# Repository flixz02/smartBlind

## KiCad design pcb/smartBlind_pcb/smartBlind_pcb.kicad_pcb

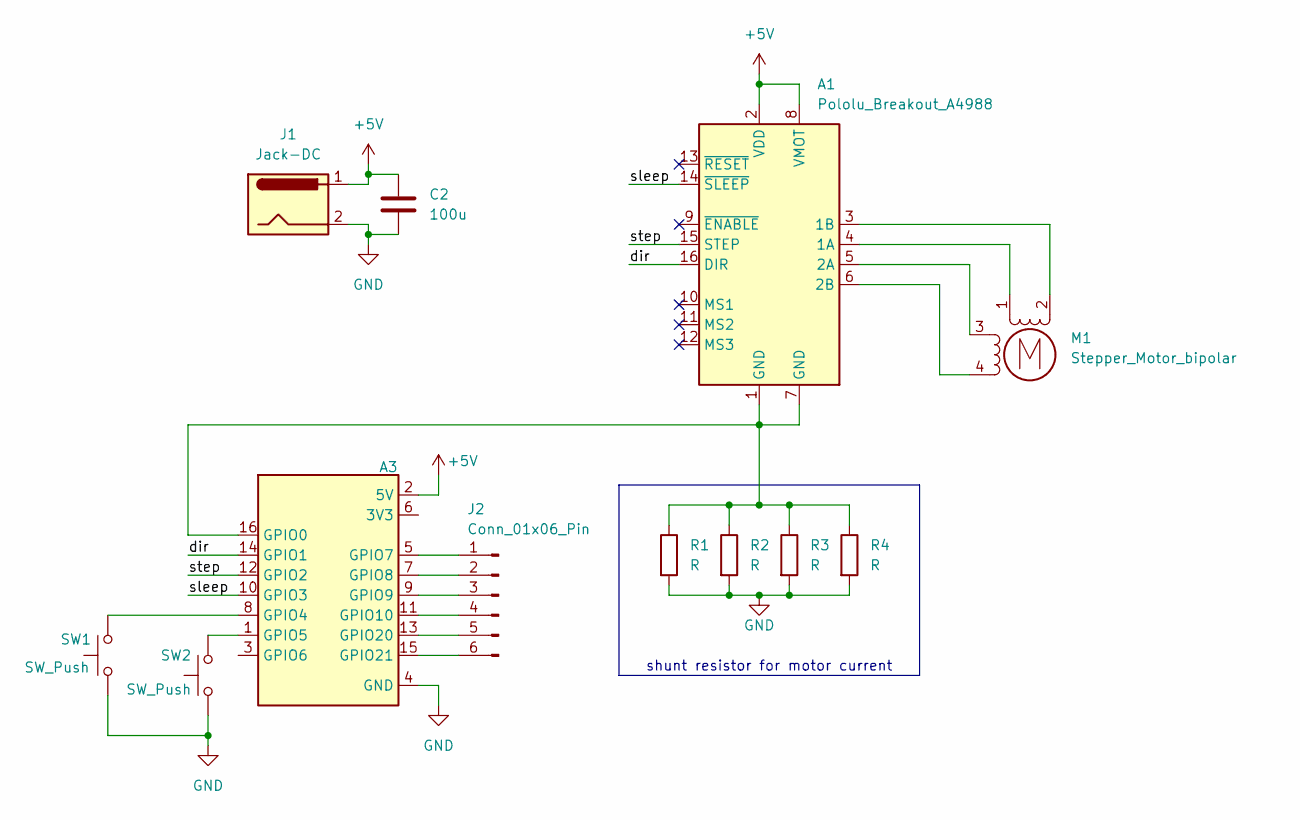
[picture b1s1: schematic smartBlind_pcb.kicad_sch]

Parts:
A1: Pololu_Breakout_A4988; Pololu_Breakout-16_15.2x20.3mm
A3: esp32-c3-supermini
C2: 100u; CP_Radial_D8.0mm_P2.50mm
J1: Jack-DC; PinHeader_1x02_P2.54mm_Vertical
J2: Conn_01x06_Pin; PinHeader_1x06_P2.54mm_Vertical
M1: Stepper_Motor_bipolar; PinHeader_1x04_P2.54mm_Vertical
R1, R2, R3, R4: R; R_Axial_DIN0204_L3.6mm_D1.6mm_P5.08mm_Horizontal
SW1, SW2: SW_Push; SW_PUSH_6mm

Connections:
+5V: A1.2 (VDD), A1.8 (VMOT), A3.2 (5V), C2.2, J1.1
/dir: A1.16 (DIR), A3.14 (GPIO1)
/sleep: A1.14 (~SLEEP), A3.10 (GPIO3)
/step: A1.15 (STEP), A3.12 (GPIO2)
GND: A3.4 (GND), C2.1, J1.2, R1.2, R2.2, R3.2, R4.2, SW1.1, SW2.1
unnamed: A1.4 (1A), M1.1
unnamed: A1.3 (1B), M1.2 (-)
unnamed: A1.5 (2A), M1.3
unnamed: A1.6 (2B), M1.4
unnamed: A1.1 (GND), A1.7 (GND), A3.16 (GPIO0), R1.1, R2.1, R3.1, R4.1
unnamed: A3.8 (GPIO4), SW1.2
unnamed: A3.1 (GPIO5), SW2.2
unnamed: A3.5 (GPIO7), J2.1
unnamed: A3.7 (GPIO8), J2.2
unnamed: A3.9 (GPIO9), J2.3
unnamed: A3.11 (GPIO10), J2.4
unnamed: A3.13 (GPIO20), J2.5
unnamed: A3.15 (GPIO21), J2.6

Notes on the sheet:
shunt resistor for motor current

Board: 2 copper layers, 12 parts (0 on the bottom side), 18 nets, no tracks yet.

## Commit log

2025-03-15 cleanup
2025-03-18 working software endstop
2025-03-20 first steps towards remembering blind position and integrating home assistant
2025-03-23 added functions for storing state and blind position
2025-03-25 added startup logic, changed blind state and blind position functions
